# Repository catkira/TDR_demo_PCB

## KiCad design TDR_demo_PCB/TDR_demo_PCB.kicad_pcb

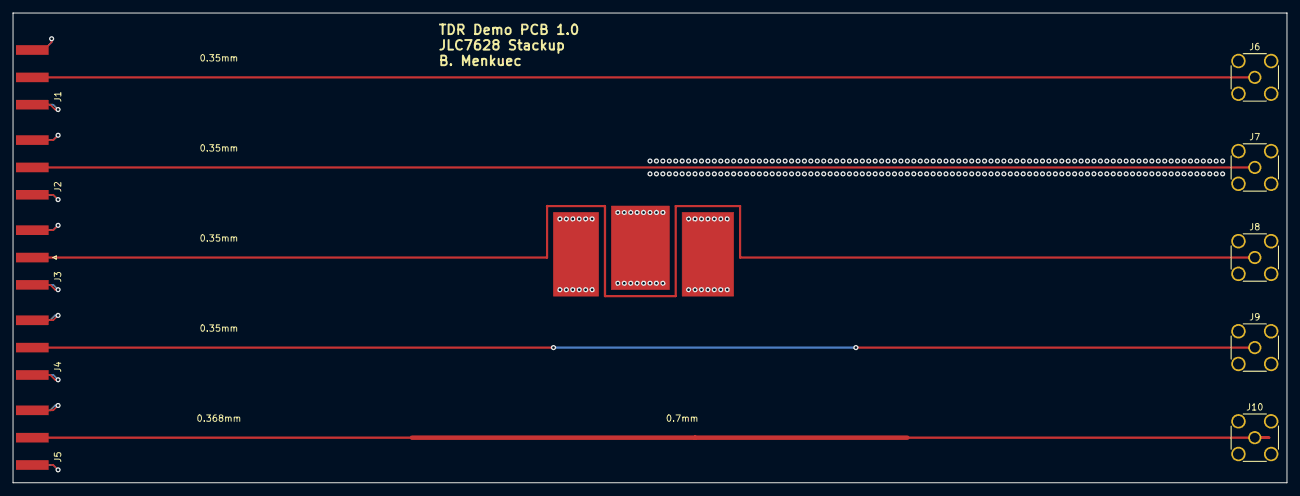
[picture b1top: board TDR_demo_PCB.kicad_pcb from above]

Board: 4 copper layers, 198.0 x 73.0 mm, 10 parts (0 on the bottom side), 6 nets.

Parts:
J1, J2, J3, J4, J5: Conn_Coaxial; SMA_Amphenol_132289_EdgeMount
J6, J7, J8, J9, J10: Conn_Coaxial; SMA_Amphenol_132134_Vertical

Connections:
GND: J1.2, J2.2, J3.2, J4.2, J5.2, J6.2, J7.2, J8.2, J9.2, J10.2
unnamed: J1.1, J6.1
unnamed: J2.1, J7.1
unnamed: J3.1, J8.1
unnamed: J4.1, J9.1
unnamed: J5.1, J10.1

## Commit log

2022-10-17 version 1.0
